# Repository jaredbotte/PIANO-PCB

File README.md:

# P.I.A.N.O PCB Repository
This repository currently contains all the KiCad files for the P.I.A.N.O PCB.    

To clone this repository, please run:   
```
git clone https://github.com/jaredbotte/PIANO-PCB.git
cd PIANO-PCB
git submodule init
git submodule update
```

This will ensure that you have all the required parts libraries to view our PCB.

I tried my best to ensure that all paths are relative, but if a path cannot be found, please try looking in the "manage libraries" or "manage footprints" tabs.

TODO: Prune this and include minimal files from external repositories!

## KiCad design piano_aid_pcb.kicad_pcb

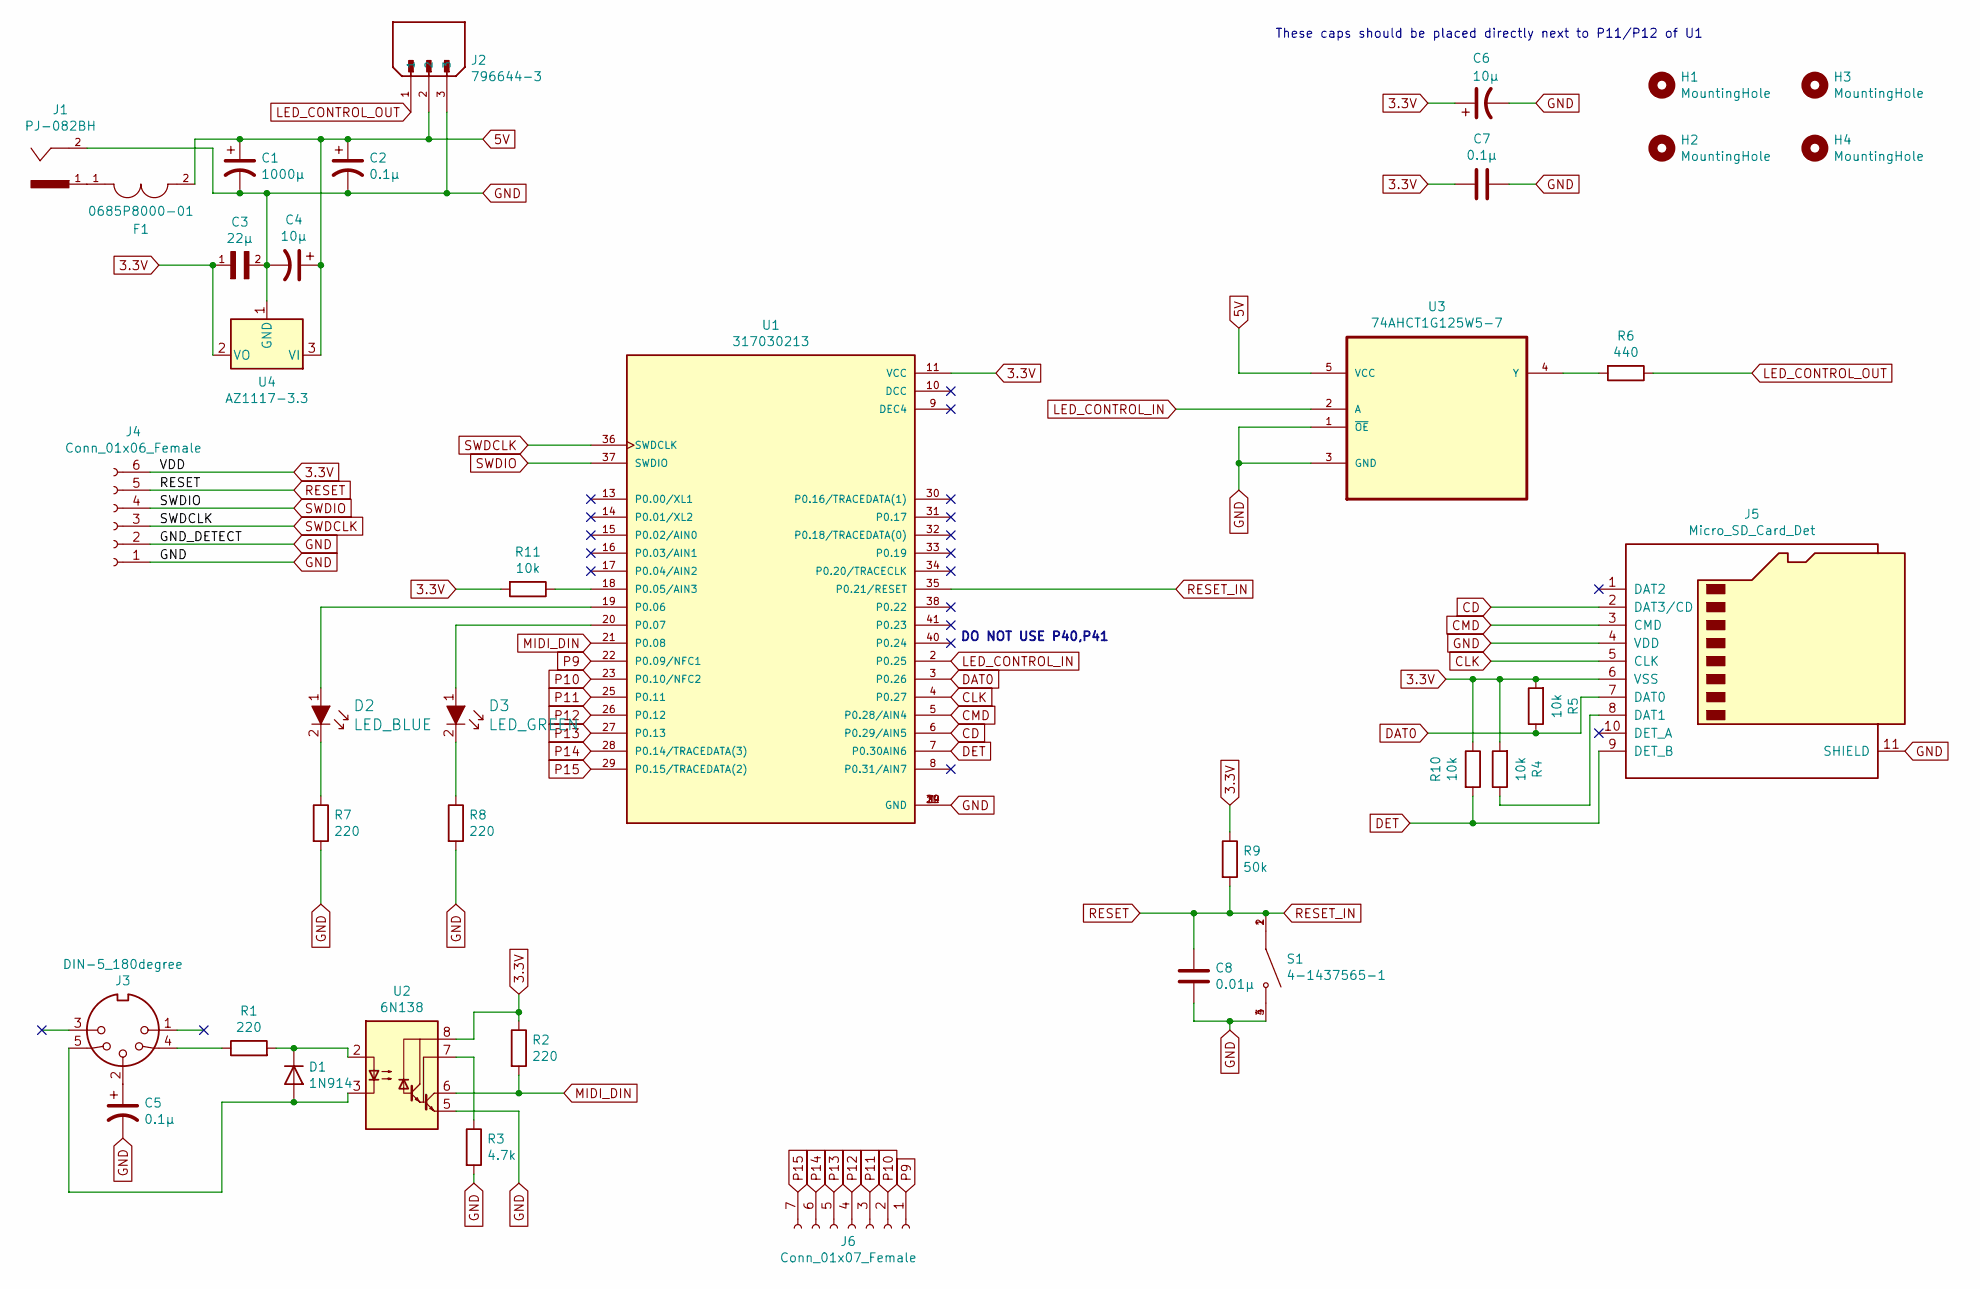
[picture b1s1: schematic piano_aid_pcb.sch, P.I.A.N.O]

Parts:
C1: 1000µ; CP_Radial_D10.0mm_P5.00mm
C2, C5, C7: 0.1µ; C_0805_2012Metric_Pad1.15x1.40mm_HandSolder
C3: 22µ; CAPC3216X110N
C4, C6: 10µ; C_0805_2012Metric_Pad1.15x1.40mm_HandSolder
C8: 0.01µ; C_0805_2012Metric_Pad1.15x1.40mm_HandSolder
D1: 1N914; D_DO-35_SOD27_P7.62mm_Horizontal
D2: LED_BLUE; LED_0805_2012Metric_Pad1.15x1.40mm_HandSolder; MPN LTST-C191TBKT; Digi-Key_PN 160-1647-1-ND
D3: LED_GREEN; LED_0805_2012Metric_Pad1.15x1.40mm_HandSolder; MPN LG L29K-G2J1-24-Z; Digi-Key_PN 475-2709-1-ND
F1: 0685P8000-01; FUSC3215X83N; PARTREV Jan2019
H1, H2, H3, H4: MountingHole; MountingHole_2.2mm_M2
J1: PJ-082BH; CUI_PJ-082BH
J2: 796644-3; TE_796644-3
J3: DIN-5_180degree; 57PC5F
J4: Conn_01x06_Female; PinSocket_1x06_P2.54mm_Vertical
J5: Micro_SD_Card_Det; MICROSD
J6: Conn_01x07_Female; PinSocket_1x07_P2.54mm_Vertical
R1, R2, R7, R8: 220; R_0805_2012Metric_Pad1.15x1.40mm_HandSolder
R3: 4.7k; R_0805_2012Metric_Pad1.15x1.40mm_HandSolder
R4, R5, R10, R11: 10k; R_0805_2012Metric_Pad1.15x1.40mm_HandSolder
R6: 440; R_0805_2012Metric_Pad1.15x1.40mm_HandSolder
R9: 50k; R_0805_2012Metric_Pad1.15x1.40mm_HandSolder
S1: 4-1437565-1; SW_4-1437565-1
U1: 317030213; XCVR_317030213
U2: 6N138; DIP-8_W7.62mm
U3: 74AHCT1G125W5-7; SOT95P280X140-5N; MPN 74AHCT1G125W5-7
U4: AZ1117-3.3; Diodes_Inc.-SOT223-03_2017-0-MFG

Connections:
3.3V: C3.1, C6.1, C7.2, J4.6, J5.6 (VSS), R2.1, R4.2, R5.2, R9.1, R10.1, R11.2, U1.11 (VCC), U2.8 (VCC), U4.2 (VO)
5V: C1.1, C2.1, C4.1, F1.2, J2.2, U3.5 (VCC), U4.3 (VI)
CD: J5.2 (DAT3/CD), U1.6 (P0.29/AIN5)
CLK: J5.5 (CLK), U1.4 (P0.27)
CMD: J5.3 (CMD), U1.5 (P0.28/AIN4)
DAT0: J5.7 (DAT0), R5.1, U1.3 (P0.26)
DET: J5.9 (DET_B), R10.2, U1.7 (P0.30AIN6)
GND: C1.2, C2.2, C3.2, C4.2, C5.2, C6.2, C7.1, C8.2, J1.2, J2.3, J4.1, J4.2, J5.4 (VDD), J5.11 (SHIELD), R3.2, R7.2, R8.2, S1.3, S1.4, U1.1 (GND), U1.12 (GND), U1.24 (GND), U1.39 (GND), U2.5 (GND), U3.1 (~OE), U3.3 (GND), U4.1 (GND)
LED_CONTROL_IN: U1.2 (P0.25), U3.2 (A)
LED_CONTROL_OUT: J2.1, R6.1
MIDI_DIN: R2.2, U1.21 (P0.08), U2.6 (VO2)
unnamed: C5.1, J3.2
unnamed: D1.1 (K), R1.2, U2.2 (C1)
unnamed: D1.2 (A), J3.5, U2.3 (C2)
unnamed: D2.1, U1.19 (P0.06)
unnamed: D2.2, R7.1
unnamed: D3.1, U1.20 (P0.07)
unnamed: D3.2, R8.1
unnamed: F1.1, J1.1
unnamed: J3.4, R1.1
unnamed: J5.8 (DAT1), R4.1
unnamed: R3.1, U2.7 (VO1)
unnamed: R6.2, U3.4 (Y)
unnamed: R11.1, U1.18 (P0.05/AIN3)
P9: J6.1, U1.22 (P0.09/NFC1)
P10: J6.2, U1.23 (P0.10/NFC2)
P11: J6.3, U1.25 (P0.11)
P12: J6.4, U1.26 (P0.12)
P13: J6.5, U1.27 (P0.13)
P14: J6.6, U1.28 (P0.14/TRACEDATA(3))
P15: J6.7, U1.29 (P0.15/TRACEDATA(2))
RESET: C8.1, J4.5, R9.2, S1.1, S1.2, U1.35 (P0.21/RESET)
SWDCLK: J4.3, U1.36 (SWDCLK)
SWDIO: J4.4, U1.37 (SWDIO)

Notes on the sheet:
These caps should be placed directly next to P11/P12 of U1
DO NOT USE P40,P41

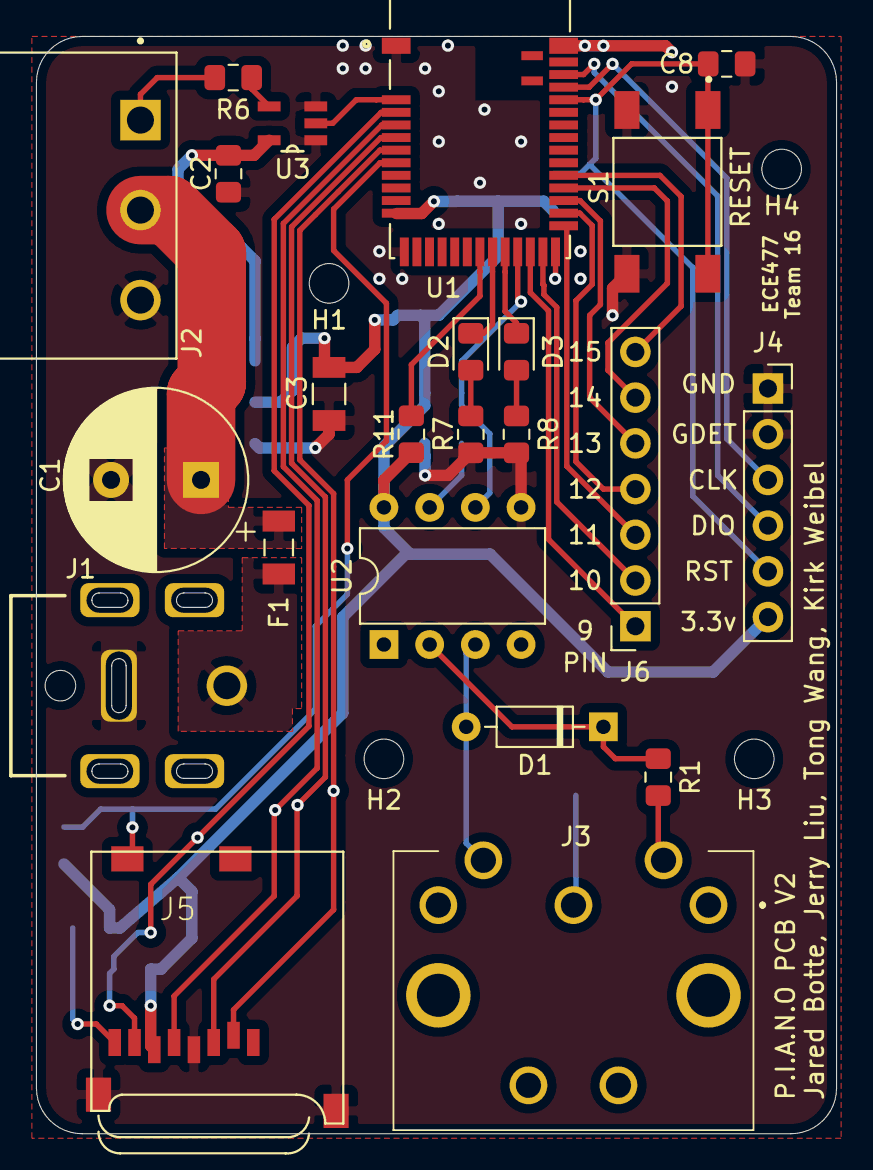
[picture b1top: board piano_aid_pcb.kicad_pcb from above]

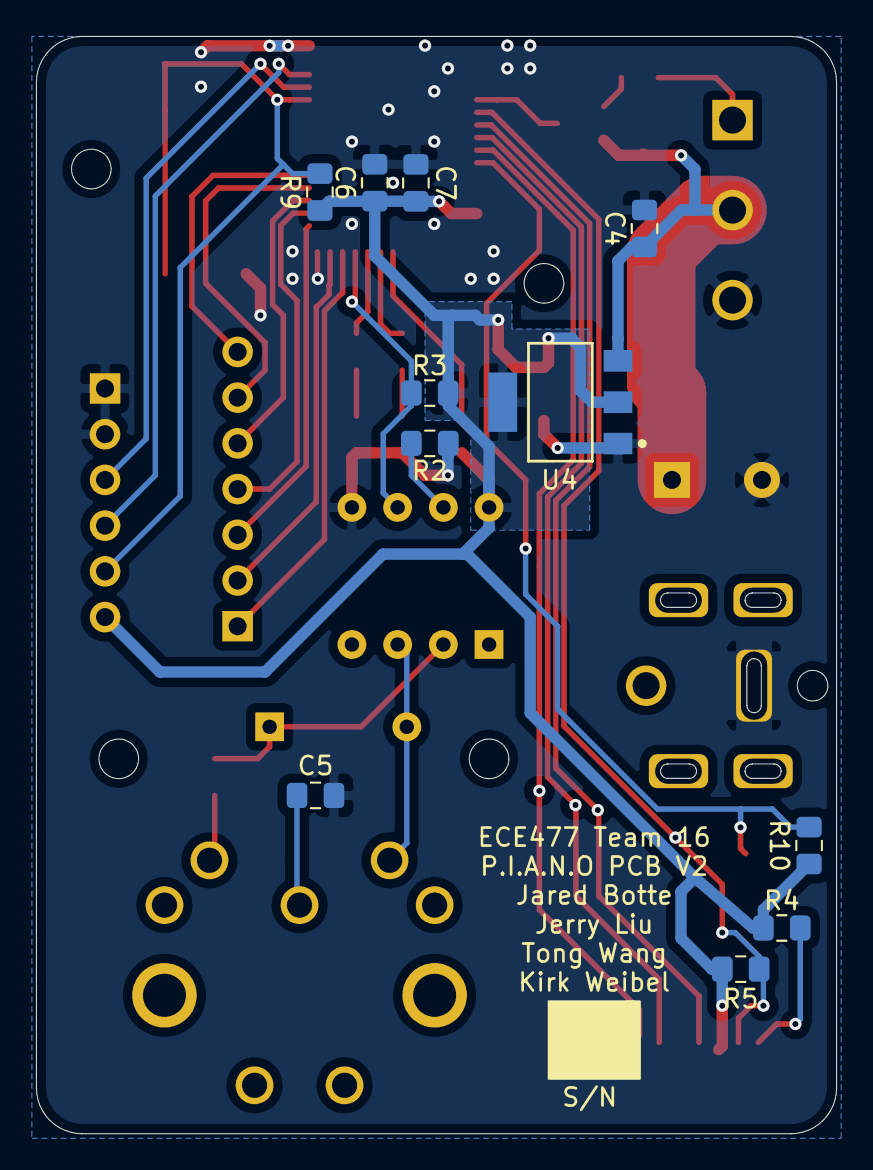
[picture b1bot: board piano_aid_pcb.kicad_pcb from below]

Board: 2 copper layers, 44.5 x 61.0 mm, 38 parts (11 on the bottom side), 34 nets.

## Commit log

2021-09-15 Initial commit. Board includes main chip, microsd, barrel jack, and MIDI DIN circuit.
2021-09-15 Added placeholder readme
2021-09-17 Added screw terminal and power regulation
2021-09-17 Added more connections
2021-09-17 Added more caps
2021-09-17 Added power supply to logic level converter
2021-09-18 Updated MIDI-DIN
2021-09-18 Added sdcard pull up to unused pin per kingston specifications
2021-09-18 Added Jerry to authors
2021-09-19 Added component labels
2021-09-20 Moved parts folder to be inside PCB directory. This should fix broken links to references
2021-09-20 Added parts folder
2021-09-21 Added LEDs, fixed absolute paths linked to my specific path
2021-09-23 Added refs to components
2021-09-23 Added kicad libraries from adafruit and digkey
2021-09-23 Added adafruit eagle libraries. Also Started assigning components to footprints
2021-09-24 Changed to https instead of ssh cloning for submodules
2021-09-24 Started board layout. Finished footprints
2021-09-28 Made PCB. Not happy with the traces, may try again. For now this is 95% complete.
2021-09-29 Completely re-traced and layed out board. Presenting PCB V2
2021-09-29 Made some adjustments. Fixed silkscreen. Added team info.
2021-09-29 Fixed some silkscreen issues. Also fixed microsd footprint and added chip detect functionality
2021-09-29 Added BOM
2021-09-30 Changed out barrel jack. Still needs to be connected to ground. I think there's an issue with the footprint. Also rounded the edges of the board.
2021-10-01 Created new plots, fixed barrel jack footprint, added thermal pad for power regulator, fixed fills. Instructors approve so far.
2021-10-01 Added power reg 3d model
2021-10-01 Updated readme to include clone instructions
2021-10-01 Added gitignore, removed fp-info-cache
2021-10-05 Fixed absolute paths, added pull up resistor.
2021-10-07 Made schematic a bit neater
2021-10-07 Fixed keepout zone, cleaned traces
2021-10-08 increased 3.3v plane on footprint
2021-10-12 Made final changes, added team/course number, fixed reset button pinout
2021-10-13 Added via for button second ground
2021-10-13 Removed unused libraries to reduce project size
2021-10-19 Added 1206 fuse
2021-10-19 Added reccomended vias
2021-10-19 Fixed thermal reliefs
